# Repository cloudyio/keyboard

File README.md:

# Cloudboard

A low profile ergo keyboard inspired by the lily 58.

## Overview

The cloudboard is a small low profile keyboard made to be wireless and bluetooth, it features a lily 58 key layout, 110mAh batteriea im each half and 2 supermini controllers

The keyboard uses ZMK for its firmware due to how simple but effective it is for ergo and bluetooth keyboards.

## Why i made the project

Ive wanted to try out a ergo keyboard for a while now and thought it would be a fun idea to make one with the features i actually want and none of the extra parts.

## Features:

### Simple design

The keyboard is made to be clean and compact with each half only being less then 15cm long, the layout used is also concidered a intro ergo keyboard layout having many similarities to a normal layout which makes it easy to learn!

*Dev board risen to represent height of header*

### NRF52840 Board

The nice!nano is conciderably one of the best boards for a ergo split keyboard, this is due to its small size while still packing bluetooth compatibility, built in battery managment and USB C. One of the biggest issues with the board though is its 20 dollar price point so instead the keyboard uses a replicate alternative which includes **all** the features of the nice!nano (can be found in BOM below).

TLDR:

The dev board allows for bluetooth, usb c and battery managment for less than 4 dollars.

### Low profile

Low profile keyboard are better ergonimically, are smaller, lighter and arguably look better. The keyboard features choc v1 switches to give the board a even lower size profile and sound profile.

## Schematics/PCB

Both schematics are the exact same

## BOM

| Item | Count | Price Per Item | Total Cost | Source | Notes |
|------|-------|----------------|------------|--------|-------|
| NRF52840 Development Board | 2 | $2.94 | $7.92 | [AliExpress](https://www.aliexpress.com/item/1005001621678794.html?spm=a2g0o.cart.0.0.272a38daeUtKrN&mp=1&pdp_npi=5%40dis%21USD%21USD%202.94%21USD%202.94%21%21USD%202.94%21%21%21%402103864c17546871093517142e0f12%2112000016846541261%21ct%21UK%21-1%21%212%210) | Cheap nice!nano + shipping for all of aliexpress items |
| 1N4148 DO-35 Diodes | 1 | $1.58 | $1.58 | [AliExpress](https://www.aliexpress.com/item/1005007131309837.html?spm=a2g0o.cart.0.0.272a38daeUtKrN&mp=1&pdp_npi=5%40dis%21USD%21USD%202.55%21USD%201.58%21%21USD%201.58%21%21%21%402103864c17546871093517142e0f12%2112000039509276484%21ct%21UK%21-1%21%211%210) | Diodes |
| Keycap Set | 1 | $32.47 | $32.47 | [AliExpress](https://www.aliexpress.com/item/1005007511714496.html?spm=a2g0o.detail.0.0.4a7bOK6zOK6zd4&mp=1&pdp_npi=5%40dis%21USD%21USD%2029.94%21USD%2027.74%21%21USD%2027.74%21%21%21%40211b613917543927371393706e2a71%2112000041079406832%21ct%21UK%214899091290%21%211%210) | keycap set, quite good quality and look very nice, most price to performacnce i could find |
| JST battery connector  | 1 | $2 | $2 | [AliExpress](https://www.aliexpress.com/item/1005008970428474.html?spm=a2g0o.cart.0.0.272a38daeUtKrN&mp=1&pdp_npi=5%40dis%21USD%21USD%201.74%21USD%201.74%21%21USD%201.74%21%21%21%402103864c17546871093517142e0f12%2112000047412491082%21ct%21UK%21-1%21%211%210) | Battery connector, comes with 2 |
| power switch | 1 | $2 | $2 | [AliExpress](https://www.aliexpress.com/item/1005006827258573.html?spm=a2g0o.cart.0.0.272a38daeUtKrN&mp=1&pdp_npi=5%40dis%21USD%21USD%201.56%21USD%201.56%21%21USD%201.56%21%21%21%402103864c17546871093517142e0f12%2112000038431123036%21ct%21UK%21-1%21%211%210) | Also comes with 2 |
| Reset tactile button | 2 | $0 | $1 | [AliExpress](https://www.aliexpress.com/item/1005006292427731.html?spm=a2g0o.cart.0.0.272a38daeUtKrN&mp=1&pdp_npi=5%40dis%21USD%21USD%200.41%21USD%200.41%21%21USD%200.41%21%21%21%402103864c17546871093517142e0f12%2112000036636688325%21ct%21UK%21-1%21%212%210) | Again, comes with 2 |
| Lithium Battery 110mAh | 1 | $8 | 8$ | [AliExpress](https://www.aliexpress.com/item/1005009279554068.html?spm=a2g0o.cart.0.0.272a38daeUtKrN&mp=1&pdp_npi=5%40dis%21USD%21USD%2014.17%21USD%207.79%21%21USD%207.79%21%21%21%402103864c17546871093517142e0f12%2112000048591585127%21ct%21UK%21-1%21%211%210) | Pretty cheap batteries, has the pcb integrated and fits under the dev board to stay hidden 2/pc |
| L+R PCB | 1 | $15.00 | $22.00 | [JLCPCB](https://cart.jlcpcb.com/quote?rand=0.6702360434866385) | Both pcbs, includes customs + shipping |
| Kailh Choc v1 Low Profile Switches | 1 | $38 | 38$ | [AliExpress](https://www.aliexpress.com/item/1005006626760418.html?spm=a2g0o.cart.0.0.272a38daeUtKrN&mp=1&pdp_npi=5%40dis%21USD%21USD%2038.48%21USD%2038.48%21%21USD%2038.48%21%21%21%402103864c17546871093517142e0f12%2112000040228314274%21ct%21UK%21-1%21%211%210&pdp_ext_f=%7B%22cart2PdpParams%22%3A%7B%22pdpBusinessMode%22%3A%22retail%22%7D%7D) | Pretty good switches for a good price, only need 60 since keyboard is 58 keys |
| Black fillament | 1 | $18 | $25 | [Amazon](https://www.amazon.co.uk/gp/product/B0CD77VHBZ/ref=sw_img_1?smid=A2AC9IE1506MQ8&psc=1) | Grey fillament that's cheap, includes shipping |
| Heat inserts | 1 | $1.70 | $1.70 | [AliExpress](https://www.aliexpress.com/item/1005008666672949.html?spm=a2g0o.productlist.main.1.ca0120e5XnvkcI&algo_pvid=65c3fc17-1755-45b7-85bb-becc4f9a3a66&algo_exp_id=65c3fc17-1755-45b7-85bb-becc4f9a3a66-0&pdp_ext_f=%7B%22order%22%3A%222513%22%2C%22eval%22%3A%221%22%7D&pdp_npi=4%40dis%21USD%211.85%210.99%21%21%211.85%210.99%21%402103835e17543530241436264e5646%2112000046157335300%21sea%21UK%210%21ABX&curPageLogUid=fu29zqBtC1Cv&utparam-url=scene%3Asearch%7Cquery_from%3A) |  Heat inserts so fillament doesnt get destroyed, they annoyingly only come in 50 but there cheap so its fine anyway |
|  |  |  | $140.79 |  |  |
|  |  |  |  |  |  |
|  |  |  |  |  |  |
|  |  |  |  |  |  |
|   |  |  |  |  |  |
notes:

- VAT is included but shipping is not since it varies, will typically end up at arround 7-15 dollars
- to save 5 dollars or so use the panel.zip gerber which is the 2 pcbs connected via mouse bites

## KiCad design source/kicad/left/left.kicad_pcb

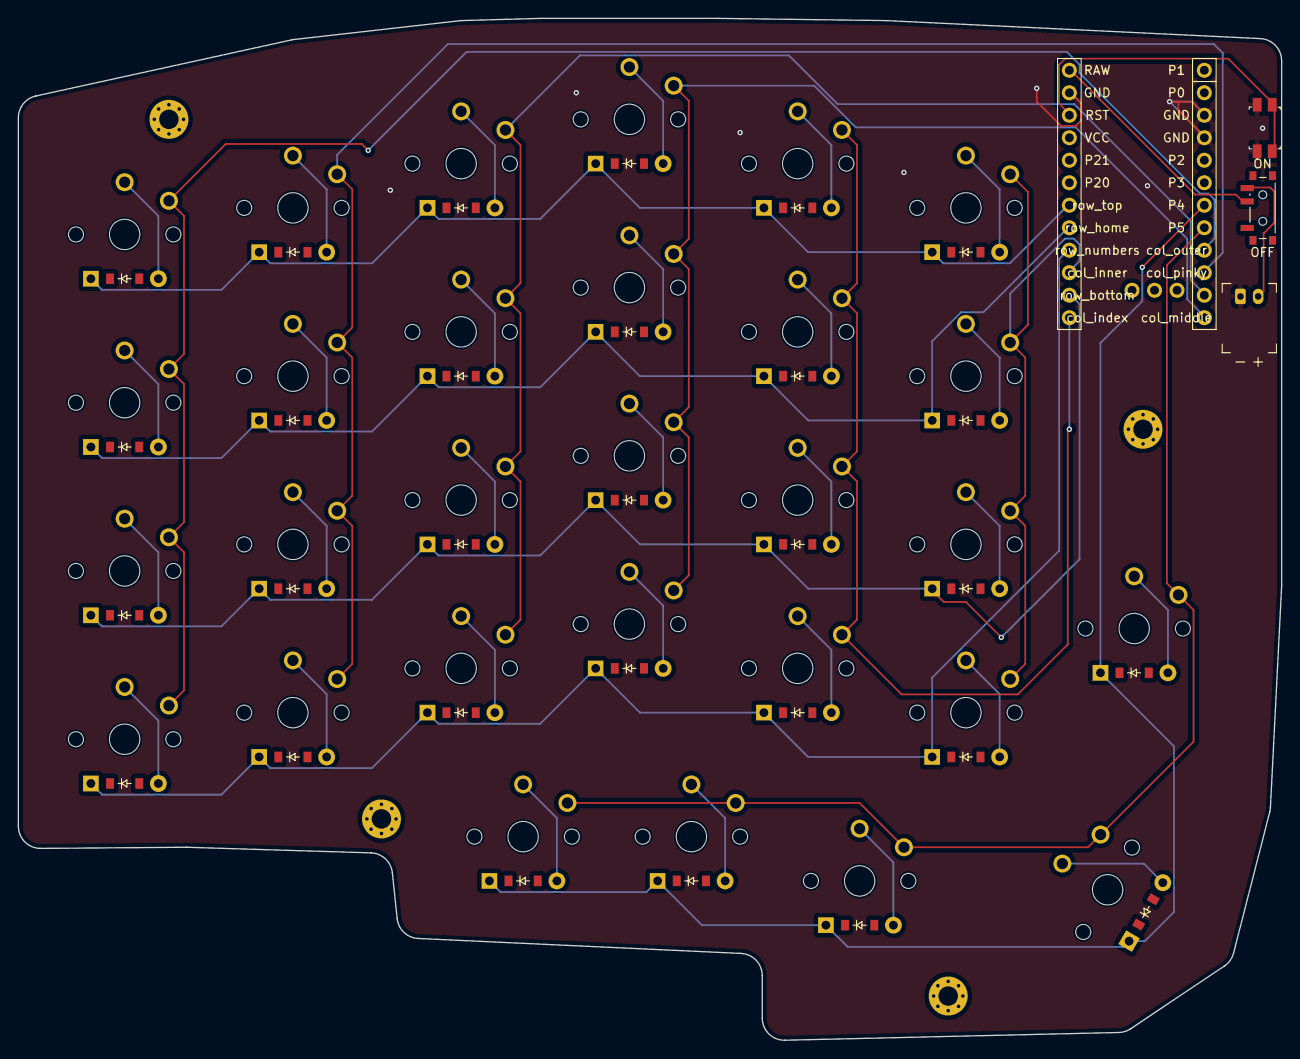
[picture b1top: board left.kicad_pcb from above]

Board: 2 copper layers, 142.7 x 115.4 mm, 66 parts (0 on the bottom side), 45 nets.

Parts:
D1, D2, D3, D4, D5, D6, D7, D8, D9, D10, D11, D12, D13, D14, D15, D16, D17, D18, D19, D20, D21, D22, D23, D24, D25, D26, D27, D28, D29: ComboDiode
JST1: battery_connector_jst_ph_2
MCU1: mcu_supermini_nrf52840
PWR1: power_switch_smd_side
RST1: reset_switch_smd_side
S1, S2, S3, S4, S5, S6, S7, S8, S9, S10, S11, S12, S13, S14, S15, S16, S17, S18, S19, S20, S21, S22, S23, S24, S25, S26, S27, S28, S29: PG1350
_1, _2, _3, _4: MountingHole_2.2mm_M2_Pad_Via

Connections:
BAT_P: JST1.2, PWR1.3
GND: JST1.1, MCU1.3, MCU1.4, MCU1.23, RST1.2, RST1.4
RAW: MCU1.24, PWR1.2
RST: MCU1.22, RST1.1, RST1.3
center_only: D26.2, S26.2
col_index: MCU1.13, S17.1, S18.1, S19.1, S20.1
col_inner: MCU1.15, S21.1, S22.1, S23.1, S24.1
col_middle: MCU1.12, S13.1, S14.1, S15.1, S16.1
col_outer: MCU1.9, S1.1, S2.1, S3.1, S4.1
col_pinky: MCU1.10, S5.1, S6.1, S7.1, S8.1
col_ring: MCU1.11, S9.1, S10.1, S11.1, S12.1
extra_col: MCU1.8, S25.1, S26.1, S27.1, S28.1, S29.1
extra_key: D29.2, S29.2
extra_row: D25.1, D26.1, D27.1, D28.1, D29.1, MCU1.7
index_bottom: D18.2, S18.2
index_home: D19.2, S19.2
index_numbers: D17.2, S17.2
index_top: D20.2, S20.2
inner_bottom: D22.2, S22.2
inner_home: D23.2, S23.2
inner_numbers: D21.2, S21.2
inner_top: D24.2, S24.2
left_only: D25.2, S25.2
macro_key: D28.2, S28.2
middle_bottom: D14.2, S14.2
middle_home: D15.2, S15.2
middle_numbers: D13.2, S13.2
middle_top: D16.2, S16.2
outer_bottom: D2.2, S2.2
outer_home: D3.2, S3.2
outer_numbers: D1.2, S1.2
outer_top: D4.2, S4.2
pinky_bottom: D6.2, S6.2
pinky_home: D7.2, S7.2
pinky_numbers: D5.2, S5.2
pinky_top: D8.2, S8.2
right_only: D27.2, S27.2
ring_bottom: D10.2, S10.2
ring_home: D11.2, S11.2
ring_numbers: D9.2, S9.2
ring_top: D12.2, S12.2
row_bottom: D2.1, D6.1, D10.1, D14.1, D18.1, D22.1, MCU1.14
row_home: D3.1, D7.1, D11.1, D15.1, D19.1, D23.1, MCU1.17
row_numbers: D1.1, D5.1, D9.1, D13.1, D17.1, D21.1, MCU1.16
row_top: D4.1, D8.1, D12.1, D16.1, D20.1, D24.1, MCU1.18

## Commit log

2025-06-14 Added layout
2025-06-14 Rename keyboard-layout.jpg to static/layout.jpg
2025-07-02 Update journal.md ( also changed an overexagarated time )
2025-07-31 done
2025-08-05 added case and made panel for cheaper production
2025-08-05 done?
2025-08-06 added firmware
2025-08-07 added full components
2025-08-07 added shapr file just in case
2025-08-07 Added the journal logs from the rereviews
2025-08-07 moved all CAD into a CAD folder
2025-08-07 Wanted to make sure everything was correct
2025-08-08 Fixed readme error
2025-08-08 updated bom
2025-08-09 Not using typeractive anymore so don’t need them there
2025-08-09 Fixed .step files
